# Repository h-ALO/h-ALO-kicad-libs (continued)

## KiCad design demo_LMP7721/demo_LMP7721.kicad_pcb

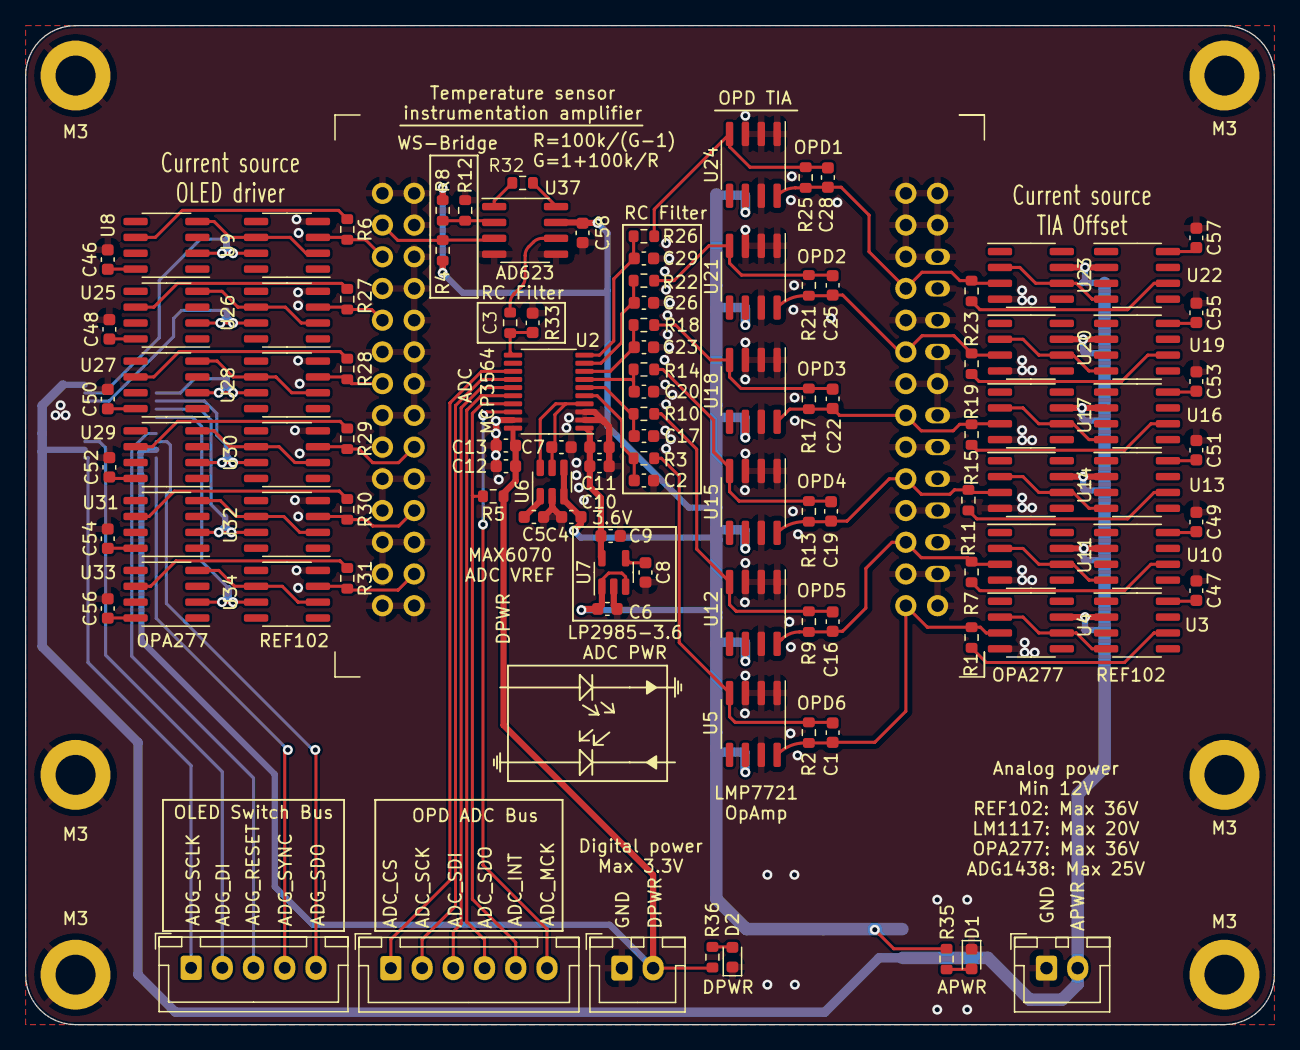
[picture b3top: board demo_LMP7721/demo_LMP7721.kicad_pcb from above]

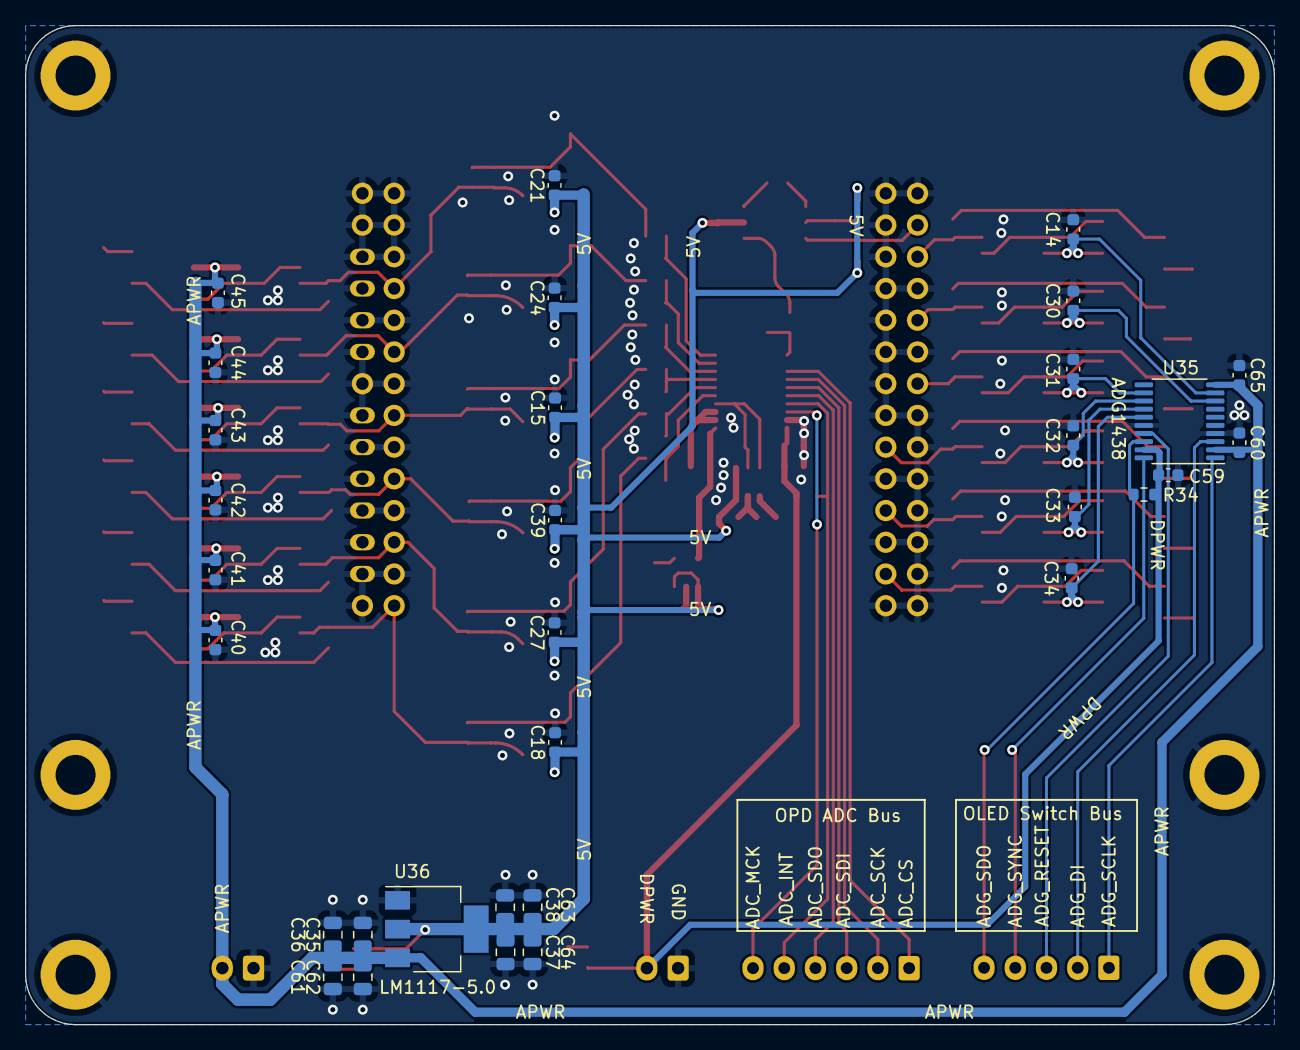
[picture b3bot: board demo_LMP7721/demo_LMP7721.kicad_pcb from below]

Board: 2 copper layers, 100.0 x 80.0 mm, 147 parts (32 on the bottom side), 93 nets.

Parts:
C1, C2, C3, C14, C15, C16, C17, C18, C19, C20, C21, C22, C23, C24, C25, C26, C27, C28, C29, C30, C31, C32, C33, C34, C39, C40, C41, C42, C43, C44, C45, C46, C47, C48, C49, C50, C51, C52, C53, C54, C55, C56, C57, C58: C; C_0603_1608Metric
C4, C5, C7, C10, C11, C12, C13, C59, C60, C65: 0.1µF; C_0603_1608Metric
C6: 1uF; C_0603_1608Metric
C8: 10nF; C_0603_1608Metric
C9: 2.2uF; C_0603_1608Metric
C35, C36, C37, C38, C61, C62, C63, C64: 1uF; C_0805_2012Metric
D1, D2: LED; LED_0603_1608Metric
H1, H2, H3, H4, H5, H6: MountingHole_Pad; MountingHole_3.2mm_M3_DIN965_Pad
J1, J3: Conn_01x02_Male; JST_XH_B2B-XH-A_1x02_P2.50mm_Vertical
J2: Conn_01x06_Male; JST_XH_B6B-XH-A_1x06_P2.50mm_Vertical
J4: Conn_01x05_Male; JST_XH_B5B-XH-A_1x05_P2.50mm_Vertical
R1, R2, R3, R4, R6, R7, R8, R9, R10, R11, R12, R13, R14, R15, R17, R18, R19, R21, R22, R23, R25, R26, R27, R28, R29, R30, R31, R32, R33, R34, R35, R36: R; R_0603_1608Metric
R5: 10k; R_0603_1608Metric
U1: h-ALO-sensor
U2: MCP3564-E/ST; TSSOP-20_4.4x6.5mm_P0.65mm
U3, U10, U13, U16, U19, U22: REF102CU; SOIC-8_3.9x4.9mm_P1.27mm
U4, U9, U11, U14, U17, U20, U23, U26, U28, U30, U32, U34: OPA277UA; SOIC-8_3.9x4.9mm_P1.27mm
U5, U12, U15, U18, U21, U24: LMP7721MA; SOIC-8_3.9x4.9mm_P1.27mm
U6: MAX6070AAUT12+T; SOT-23-6
U7: LP2985-3.3; SOT-23-5
U8, U25, U27, U29, U31, U33: REF102BU; SOIC-8_3.9x4.9mm_P1.27mm
U35: ADG1438BRUZ; TSSOP-20_4.4x6.5mm_P0.65mm
U36: LM1117-5.0; SOT-223-3_TabPin2
U37: AD623ARZ; SOIC-8_3.9x4.9mm_P1.27mm

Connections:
+5V: C4.1, C6.1, C15.2, C18.2, C21.2, C24.2, C27.2, C37.1, C38.1, C39.2, C58.1, C63.1, C64.1, R4.1, R8.1, R35.1, U5.6 (V+), U6.3 (EN), U6.4 (IN), U7.1 (VIN), U7.3 (ON/~OFF), U12.6 (V+), U15.6 (V+), U18.6 (V+), U21.6 (V+), U24.6 (V+), U36.2 (VO), U37.7 (Vs+)
/ADC_REFIN+: C7.1, U2.4 (REFIN+), U6.5 (OUTS), U6.6 (OUTF)
/OLED1+: R6.2, U1.5 (OLED1+), U9.3 (+IN)
/OLED2+: R27.2, U1.9 (OLED2+), U26.3 (+IN)
/OLED3+: R28.2, U1.13 (OLED3+), U28.3 (+IN)
/OLED4+: R29.2, U1.18 (OLED4+), U30.3 (+IN)
/OLED5+: R30.2, U1.22 (OLED5+), U32.3 (+IN)
/OLED6+: R31.2, U1.26 (OLED6+), U34.3 (+IN)
/OLED_driver0/V12: C14.1, U8.2 (Vin), U9.7 (V+), U35.9 (S4)
/OLED_driver1/V12: C30.1, U25.2 (Vin), U26.7 (V+), U35.8 (S3)
/OLED_driver2/V12: C31.1, U27.2 (Vin), U28.7 (V+), U35.12 (S8)
/OLED_driver3/V12: C32.1, U29.2 (Vin), U30.7 (V+), U35.13 (S7)
/OLED_driver4/V12: C33.1, U31.2 (Vin), U32.7 (V+), U35.14 (S6)
/OLED_driver5/V12: C34.1, U33.2 (Vin), U34.7 (V+), U35.15 (S5)
/OPD1-: C28.1, R23.1, R25.1, U1.36 (OPD1-), U23.3 (+IN), U24.8 (IN-)
/OPD2-: C25.1, R19.1, R21.1, U1.40 (OPD2-), U20.3 (+IN), U21.8 (IN-)
/OPD3-: C22.1, R15.1, R17.1, U1.44 (OPD3-), U17.3 (+IN), U18.8 (IN-)
/OPD4-: C19.1, R11.1, R13.1, U1.48 (OPD4-), U14.3 (+IN), U15.8 (IN-)
/OPD5-: C16.1, R7.1, R9.1, U1.52 (OPD5-), U11.3 (+IN), U12.8 (IN-)
/OPD6-: C1.1, R1.1, R2.1, U1.56 (OPD6-), U4.3 (+IN), U5.8 (IN-)
/Temp+: R4.2, U1.3 (Temp+), U37.3 (+)
/amp0/AMPO: C1.2, R2.2, R3.2, U5.4 (VO)
/amp1/AMPO: C16.2, R9.2, R10.2, U12.4 (VO)
/amp2/AMPO: C19.2, R13.2, R14.2, U15.4 (VO)
/amp3/AMPO: C22.2, R17.2, R18.2, U18.4 (VO)
/amp4/AMPO: C25.2, R21.2, R22.2, U21.4 (VO)
/amp5/AMPO: C28.2, R25.2, R26.2, U24.4 (VO)
ADC_AVDD: C9.1, C10.2, C11.2, U2.1 (AVDD), U7.5 (VOUT)
ADC_CH0: C2.2, R3.1, U2.5 (CH0)
ADC_CH1: C17.2, R10.1, U2.6 (CH1)
ADC_CH2: C20.2, R14.1, U2.7 (CH2)
ADC_CH3: C23.2, R18.1, U2.8 (CH3)
ADC_CH4: C26.2, R22.1, U2.9 (CH4)
ADC_CH5: C29.2, R26.1, U2.10 (CH5)
ADC_CH6: C3.1, R33.1, U2.11 (CH6)
ADC_CS: J2.1, U2.13 (*CS)
ADC_INT: J2.5, R5.2, U2.17 (*IRQ/MDAT)
ADC_MCK: J2.6, U2.18 (MCLKIN)
ADC_SCK: J2.2, U2.14 (SCK)
ADC_SDI: J2.3, U2.15 (SDI)
ADC_SDO: J2.4, U2.16 (SDO)
ADG_DI: J4.2, U35.3 (DIN)
ADG_RESET: J4.3, U35.17 (RESET)
ADG_SCLK: J4.1, U35.1 (SCLK)
ADG_SDO: J4.5, R34.2, U35.18 (SDO)
ADG_SYNC: J4.4, U35.20 (SYNC)
BATT_12V: C35.1, C36.1, C40.2, C41.2, C42.2, C43.2, C44.2, C45.2, C60.2, C61.1, C62.1, C65.2, J1.2, U3.2 (Vin), U4.7 (V+), U10.2 (Vin), U11.7 (V+), U13.2 (Vin), U14.7 (V+), U16.2 (Vin), U17.7 (V+), U19.2 (Vin), U20.7 (V+), U22.2 (Vin), U23.7 (V+), U35.2 (VDD), U35.10 (D), U36.3 (VI)
GND: C2.1, C3.2, C4.2, C5.2, C6.2, C7.2, C8.2, C9.2, C10.1, C11.1, C12.2, C13.2, C14.2, C15.1, C17.1, C18.1, C20.1, C21.1, C23.1, C24.1, C26.1, C27.1, C29.1, C30.2, C31.2, C32.2, C33.2, C34.2, C35.2, C36.2, C37.2, C38.2, C39.1, C40.1, C41.1, C42.1, C43.1, C44.1, C45.1, C46.2, C47.1, C48.2, C49.1, C50.2, C51.1, C52.2, C53.1, C54.2, C55.1, C56.2, C57.1, C58.2, C59.1, C60.1, C61.2, C62.2, C63.2, C64.2, C65.1, D1.1 (K), D2.1 (K), H1.1, H2.1, H3.1, H4.1, H5.1, H6.1, J1.1, J3.1, R12.2, U1.1 (NC), U1.2 (NC), U1.4 (NC), U1.6 (OPD1+), U1.7 (NC), U1.8 (NC), U1.10 (OPD2+), U1.11 (NC), U1.12 (NC), U1.14 (NC), U1.15 (OPD3+), U1.16 (NC), U1.17 (NC), U1.19 (OPD4+), U1.20 (NC), U1.21 (NC), U1.23 (OPD5+), U1.24 (NC), U1.25 (NC), U1.27 (OPD6+), U1.28 (NC), U1.29 (NC), U1.30 (NC), U1.31 (NC), U1.32 (Temp-), U1.33 (NC), U1.34 (NC), U1.35 (OLED1-), U1.37 (NC), U1.38 (NC), U1.39 (OLED2-), U1.41 (NC), U1.42 (NC), U1.43 (OLED3-), U1.45 (NC), U1.46 (NC), U1.47 (OLED4-), U1.49 (NC), U1.50 (NC), U1.51 (OLED5-), U1.53 (NC), U1.54 (NC), U1.55 (OLED6-), U2.2 (AGND), U2.3 (REFIN-), U2.19 (DGND), U4.4 (V-), U5.1 (IN+), U5.2 (NC), U5.3 (V-), U5.7 (NC), U6.2 (GND), U7.2 (GND), U9.4 (V-), U11.4 (V-), U12.1 (IN+), U12.2 (NC), U12.3 (V-), U12.7 (NC), U14.4 (V-), U15.1 (IN+), U15.2 (NC), U15.3 (V-), U15.7 (NC), U17.4 (V-), U18.1 (IN+), U18.2 (NC), U18.3 (V-), U18.7 (NC), U20.4 (V-), U21.1 (IN+), U21.2 (NC), U21.3 (V-), U21.7 (NC), U23.4 (V-), U24.1 (IN+), U24.2 (NC), U24.3 (V-), U24.7 (NC), U26.4 (V-), U28.4 (V-), U30.4 (V-), U32.4 (V-), U34.4 (V-), U35.4 (GND), U35.16 (VSS), U36.1 (GND), U37.4 (Vs-), U37.5 (Ref)
unnamed: C5.1, U6.1 (FILTER)
unnamed: C8.1, U7.4 (BP)
unnamed: C46.1, U8.8 (NR)
unnamed: C47.2, U3.8 (NR)
unnamed: C48.1, U25.8 (NR)
unnamed: C49.2, U10.8 (NR)
unnamed: C50.1, U27.8 (NR)
unnamed: C51.2, U13.8 (NR)
unnamed: C52.1, U29.8 (NR)
unnamed: C53.2, U16.8 (NR)
unnamed: C54.1, U31.8 (NR)
unnamed: C55.2, U19.8 (NR)
unnamed: C56.1, U33.8 (NR)
unnamed: C57.2, U22.8 (NR)
unnamed: D1.2 (A), R35.2
unnamed: D2.2 (A), R36.2
unnamed: R1.2, U3.6 (Vout)
unnamed: R6.1, U8.6 (Vout)
unnamed: R7.2, U10.6 (Vout)
unnamed: R11.2, U13.6 (Vout)
unnamed: R8.2, R12.1, U37.2 (-)
unnamed: R15.2, U16.6 (Vout)
unnamed: R19.2, U19.6 (Vout)
unnamed: R23.2, U22.6 (Vout)
unnamed: R27.1, U25.6 (Vout)
unnamed: R28.1, U27.6 (Vout)
unnamed: R29.1, U29.6 (Vout)
unnamed: R30.1, U31.6 (Vout)
unnamed: R31.1, U33.6 (Vout)
unnamed: R32.1, U37.8 (Rg)
unnamed: R32.2, U37.1 (Rg)
unnamed: R33.2, U37.6
unnamed: U3.4 (GND), U4.2 (-IN), U4.6 (OUTPUT)
unnamed: U8.4 (GND), U9.2 (-IN), U9.6 (OUTPUT)
unnamed: U10.4 (GND), U11.2 (-IN), U11.6 (OUTPUT)
unnamed: U13.4 (GND), U14.2 (-IN), U14.6 (OUTPUT)
unnamed: U16.4 (GND), U17.2 (-IN), U17.6 (OUTPUT)
unnamed: U19.4 (GND), U20.2 (-IN), U20.6 (OUTPUT)
unnamed: U22.4 (GND), U23.2 (-IN), U23.6 (OUTPUT)
unnamed: U25.4 (GND), U26.2 (-IN), U26.6 (OUTPUT)
unnamed: U27.4 (GND), U28.2 (-IN), U28.6 (OUTPUT)
unnamed: U29.4 (GND), U30.2 (-IN), U30.6 (OUTPUT)
unnamed: U31.4 (GND), U32.2 (-IN), U32.6 (OUTPUT)
unnamed: U33.4 (GND), U34.2 (-IN), U34.6 (OUTPUT)
VL: C12.1, C13.1, C59.2, J3.2, R5.1, R34.1, R36.1, U2.20 (DVDD), U35.19 (VL)

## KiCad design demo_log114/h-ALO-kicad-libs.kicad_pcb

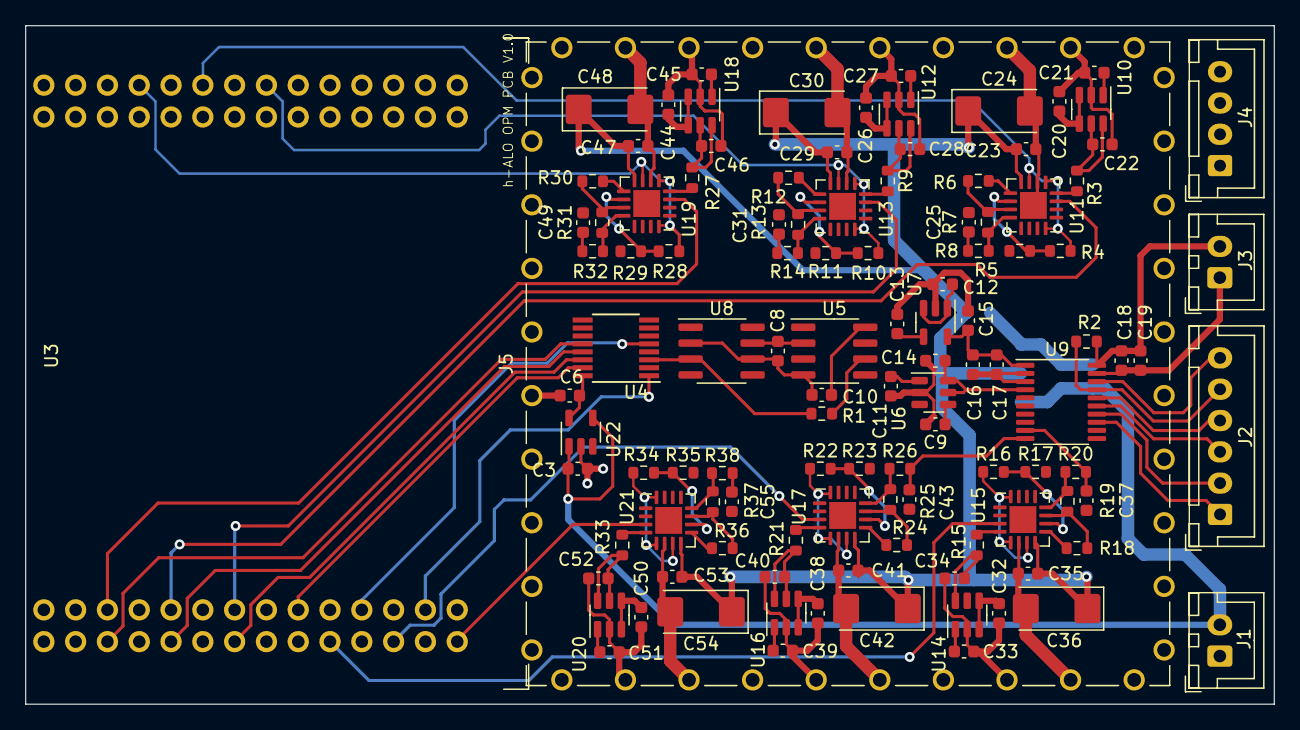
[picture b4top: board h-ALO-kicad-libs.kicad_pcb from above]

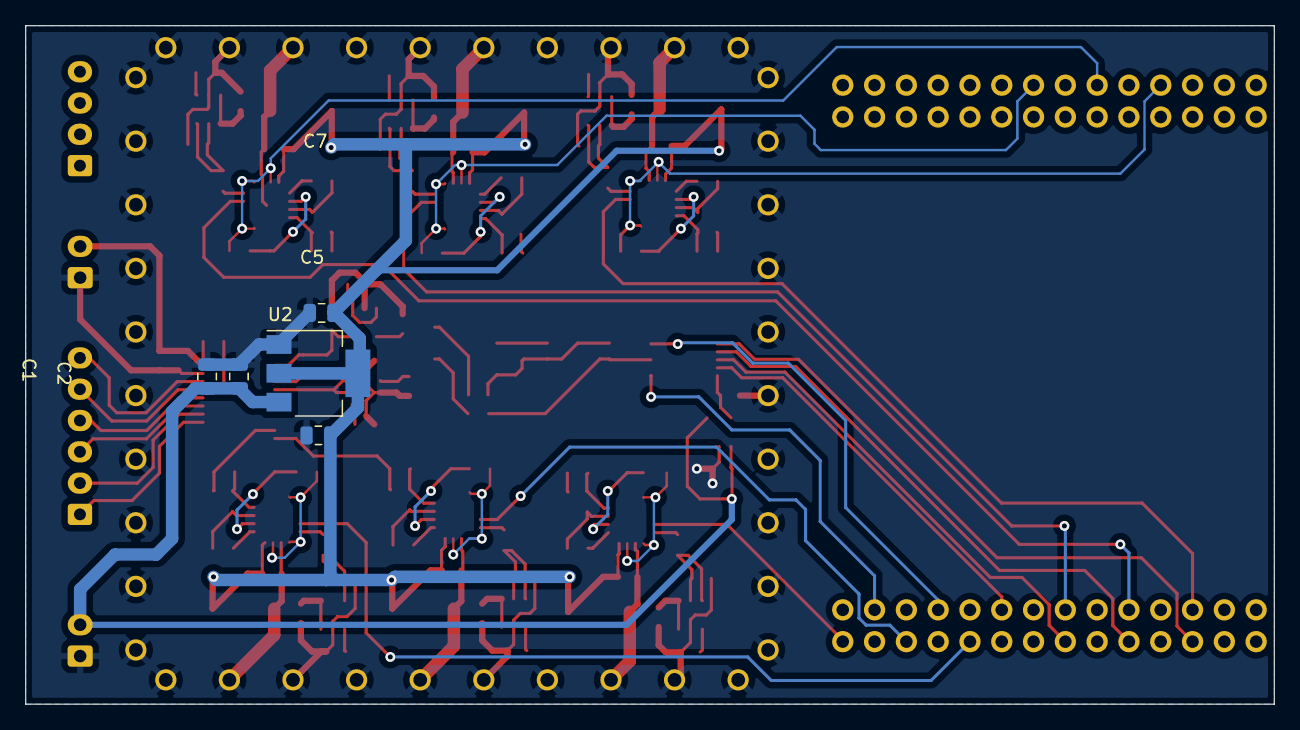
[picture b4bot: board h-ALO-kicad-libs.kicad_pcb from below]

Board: 2 copper layers, 99.7 x 54.2 mm, 118 parts (5 on the bottom side), 89 nets.

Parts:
C1, C2, C5, C7: 1uF; C_0805_2012Metric
C3, C12: 1uF; C_0603_1608Metric
C6, C8, C10, C25, C31, C37, C43, C49, C55: 1µF; C_0603_1608Metric
C9, C11, C14, C16, C17, C19, C20, C21, C22, C26, C27, C28, C32, C33, C34, C38, C39, C40, C44, C45, C46, C50, C51, C52: 0.1µF; C_0603_1608Metric
C13: 10nF; C_0603_1608Metric
C15: 2.2uF; C_0603_1608Metric
C18: 0.1uF; C_0603_1608Metric
C23, C29, C35, C41, C47, C53: 1000pF; C_0603_1608Metric
C24, C30, C36, C42, C48, C54: 10µF; CP_EIA-6032-15_Kemet-U
J1, J3: Conn_01x02_Male; JST_XH_B2B-XH-A_1x02_P2.50mm_Vertical
J2: Conn_01x06_Male; JST_XH_B6B-XH-A_1x06_P2.50mm_Vertical
J4: Conn_01x04_Male; JST_XH_B4B-XH-A_1x04_P2.50mm_Vertical
J5: RFShield_OnePiece; Wuerth_36503505_50x50mm
R1, R4, R5, R6, R7, R10, R11, R12, R13, R16, R17, R18, R19, R22, R23, R24, R25, R28, R29, R30, R31, R34, R35, R36, R37: R; R_0603_1608Metric
R2: 10k; R_0603_1608Metric
R3, R9, R15, R21, R27, R33: 1.62M; R_0603_1608Metric
R8, R14, R20, R26, R32, R38: 3k; R_0603_1608Metric
U2: LM1117-5.0; SOT-223-3_TabPin2
U3: h-ALO-sensor
U4: ADG658YRQZ-REEL7; QSOP-16_3.9x4.9mm_P0.635mm
U5: REF102BU; SOIC-8_3.9x4.9mm_P1.27mm
U6: MAX6070AAUT12+T; SOT-23-6
U7: LP2985-3.6; SOT-23-5
U8: OPA277UA; SOIC-8_3.9x4.9mm_P1.27mm
U9: MCP3564-E/ST; TSSOP-20_4.4x6.5mm_P0.65mm
U10, U12, U14, U16, U18, U20: MAX6070AAUT41+T; SOT-23-6
U11, U13, U15, U17, U19, U21: LOG114AIRGVR; QFN-16-1EP_4x4mm_P0.65mm_EP2.15x2.15mm
U22: MCP1804x-A002xOT; SOT-23-5

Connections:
+5V: C5.1, C7.1, C9.1, C12.1, C20.1, C23.1, C24.1, C26.1, C29.1, C30.1, C32.1, C35.1, C36.1, C38.1, C41.1, C42.1, C44.1, C47.1, C48.1, C50.1, C53.1, C54.1, U2.2 (VO), U6.3 (EN), U6.4 (IN), U7.1 (VIN), U7.3 (ON/~OFF), U10.3 (EN), U10.4 (IN), U11.8 (V+), U12.3 (EN), U12.4 (IN), U13.8 (V+), U14.3 (EN), U14.4 (IN), U15.8 (V+), U16.3 (EN), U16.4 (IN), U17.8 (V+), U18.3 (EN), U18.4 (IN), U19.8 (V+), U20.3 (EN), U20.4 (IN), U21.8 (V+)
/amp1/4.096V: C46.1, R27.1, U18.5 (OUTS), U18.6 (OUTF)
/amp1/+IN4: R28.2, R29.1, U19.10 (+IN4)
/amp1/-IN4: R30.2, R31.1, U19.11 (-IN4)
/amp1/I1: R27.2, U19.4 (I1)
/amp1/VLOGOUT: R30.1, U19.9 (VLOGOUT)
/amp1/VO4: R31.2, R32.1, U19.12 (VO4)
/amp2/4.096V: C22.1, R3.1, U10.5 (OUTS), U10.6 (OUTF)
/amp2/+IN4: R4.2, R5.1, U11.10 (+IN4)
/amp2/-IN4: R6.2, R7.1, U11.11 (-IN4)
/amp2/I1: R3.2, U11.4 (I1)
/amp2/VLOGOUT: R6.1, U11.9 (VLOGOUT)
/amp2/VO4: R7.2, R8.1, U11.12 (VO4)
/amp3/4.096V: C28.1, R9.1, U12.5 (OUTS), U12.6 (OUTF)
/amp3/+IN4: R10.2, R11.1, U13.10 (+IN4)
/amp3/-IN4: R12.2, R13.1, U13.11 (-IN4)
/amp3/I1: R9.2, U13.4 (I1)
/amp3/VLOGOUT: R12.1, U13.9 (VLOGOUT)
/amp3/VO4: R13.2, R14.1, U13.12 (VO4)
/amp4/4.096V: C34.1, R15.1, U14.5 (OUTS), U14.6 (OUTF)
/amp4/+IN4: R16.2, R17.1, U15.10 (+IN4)
/amp4/-IN4: R18.2, R19.1, U15.11 (-IN4)
/amp4/I1: R15.2, U15.4 (I1)
/amp4/VLOGOUT: R18.1, U15.9 (VLOGOUT)
/amp4/VO4: R19.2, R20.1, U15.12 (VO4)
/amp5/4.096V: C40.1, R21.1, U16.5 (OUTS), U16.6 (OUTF)
/amp5/+IN4: R22.2, R23.1, U17.10 (+IN4)
/amp5/-IN4: R24.2, R25.1, U17.11 (-IN4)
/amp5/I1: R21.2, U17.4 (I1)
/amp5/VLOGOUT: R24.1, U17.9 (VLOGOUT)
/amp5/VO4: R25.2, R26.1, U17.12 (VO4)
/amp6/4.096V: C52.1, R33.1, U20.5 (OUTS), U20.6 (OUTF)
/amp6/+IN4: R34.2, R35.1, U21.10 (+IN4)
/amp6/-IN4: R36.2, R37.1, U21.11 (-IN4)
/amp6/I1: R33.2, U21.4 (I1)
/amp6/VLOGOUT: R36.1, U21.9 (VLOGOUT)
/amp6/VO4: R37.2, R38.1, U21.12 (VO4)
ADC_AVDD: C15.1, C16.2, C17.2, U7.5 (VOUT), U9.1 (AVDD)
ADC_CH1: C49.1, R32.2, U9.6 (CH1)
ADC_CH2: C25.1, R8.2, U9.7 (CH2)
ADC_CH3: C31.1, R14.2, U9.8 (CH3)
ADC_CH4: C37.1, R20.2, U9.9 (CH4)
ADC_CH5: C43.1, R26.2, U9.10 (CH5)
ADC_CH6: C55.1, R38.2, U9.11 (CH6)
ADC_CS: J2.1, U9.13 (*CS)
ADC_DVDD: C18.1, C19.1, J3.2, R2.1, U9.20 (DVDD)
ADC_INT: J2.5, R2.2, U9.17 (*IRQ/MDAT)
ADC_MCK: J2.6, U9.18 (MCLKIN)
ADC_SCK: J2.2, U9.14 (SCK)
ADC_SDI: J2.3, U9.15 (SDI)
ADC_SDO: J2.4, U9.16 (SDO)
ADC_VREF+: C14.1, U6.5 (OUTS), U6.6 (OUTF), U9.4 (REFIN+)
BATT_+11V: C1.1, C2.1, C3.1, C8.1, J1.2, U2.3 (VI), U5.2 (Vin), U8.7 (V+), U22.1 (VIN), U22.4 (~SHDN)
GND: C1.2, C2.2, C3.2, C5.2, C6.2, C7.2, C9.2, C11.2, C12.2, C13.2, C14.2, C15.2, C16.1, C17.1, C18.2, C19.2, C20.2, C21.2, C22.2, C23.2, C24.2, C25.2, C26.2, C27.2, C28.2, C29.2, C30.2, C31.2, C32.2, C33.2, C34.2, C35.2, C36.2, C37.2, C38.2, C39.2, C40.2, C41.2, C42.2, C43.2, C44.2, C45.2, C46.2, C47.2, C48.2, C49.2, C50.2, C51.2, C52.2, C53.2, C54.2, C55.2, J1.1, J3.1, J5.1 (Shield), R5.2, R11.2, R17.2, R23.2, R29.2, R35.2, U2.1 (GND), U4.7 (VSS), U4.8 (GND), U6.2 (GND), U7.2 (GND), U8.4 (V-), U9.2 (AGND), U9.3 (REFIN-), U9.19 (DGND), U10.2 (GND), U11.6 (V-), U11.17 (V-), U12.2 (GND), U13.6 (V-), U13.17 (V-), U14.2 (GND), U15.6 (V-), U15.17 (V-), U16.2 (GND), U17.6 (V-), U17.17 (V-), U18.2 (GND), U19.6 (V-), U19.17 (V-), U20.2 (GND), U21.6 (V-), U21.17 (V-), U22.2 (GND)
MUX_VDD_+10V: C6.1, U4.16 (VDD), U22.5 (VOUT)
unnamed: C10.1, U5.8 (NR)
unnamed: C8.2, C10.2, U5.4 (GND), U8.2 (-IN), U8.6 (OUTPUT)
unnamed: C11.1, U6.1 (FILTER)
unnamed: C13.1, U7.4 (BP)
unnamed: C21.1, U10.1 (FILTER)
unnamed: C27.1, U12.1 (FILTER)
unnamed: C33.1, U14.1 (FILTER)
unnamed: C39.1, U16.1 (FILTER)
unnamed: C45.1, U18.1 (FILTER)
unnamed: C51.1, U20.1 (FILTER)
unnamed: R1.1, U5.6 (Vout)
OLED1+: U3.5 (OLED1+), U4.12 (S4)
OLED2+: U3.9 (OLED2+), U4.13 (S1)
OLED3+: U3.13 (OLED3+), U4.14 (S2)
OLED4+: U3.18 (OLED4+), U4.15 (S3)
OLED5+: U3.22 (OLED5+), U4.5 (S6)
OLED6+: U3.26 (OLED6+), U4.1 (S5)
OLED_A0: J4.4, U4.11 (A0)
OLED_A1: J4.3, U4.10 (A1)
OLED_A2: J4.2, U4.9 (A2)
OLED_CURRENT: R1.2, U4.3 (D), U8.3 (+IN)
OLED_EN: J4.1, U4.6 (EN)
OPD1+: U3.6 (OPD1+), U19.3 (I2)
OPD1-: R28.1, U3.36 (OPD1-), U19.5 (VCMIN), U19.7 (Com), U19.16 (VREF)
OPD2+: U3.10 (OPD2+), U11.3 (I2)
OPD2-: R4.1, U3.40 (OPD2-), U11.5 (VCMIN), U11.7 (Com), U11.16 (VREF)
OPD3+: U3.14 (OPD3+), U13.3 (I2)
OPD3-: R10.1, U3.44 (OPD3-), U13.5 (VCMIN), U13.7 (Com), U13.16 (VREF)
OPD4+: U3.19 (OPD4+), U15.3 (I2)
OPD4-: R16.1, U3.48 (OPD4-), U15.5 (VCMIN), U15.7 (Com), U15.16 (VREF)
OPD5+: U3.23 (OPD5+), U17.3 (I2)
OPD5-: R22.1, U3.52 (OPD5-), U17.5 (VCMIN), U17.7 (Com), U17.16 (VREF)
OPD6+: U3.27 (OPD6+), U21.3 (I2)
OPD6-: R34.1, U3.56 (OPD6-), U21.5 (VCMIN), U21.7 (Com), U21.16 (VREF)

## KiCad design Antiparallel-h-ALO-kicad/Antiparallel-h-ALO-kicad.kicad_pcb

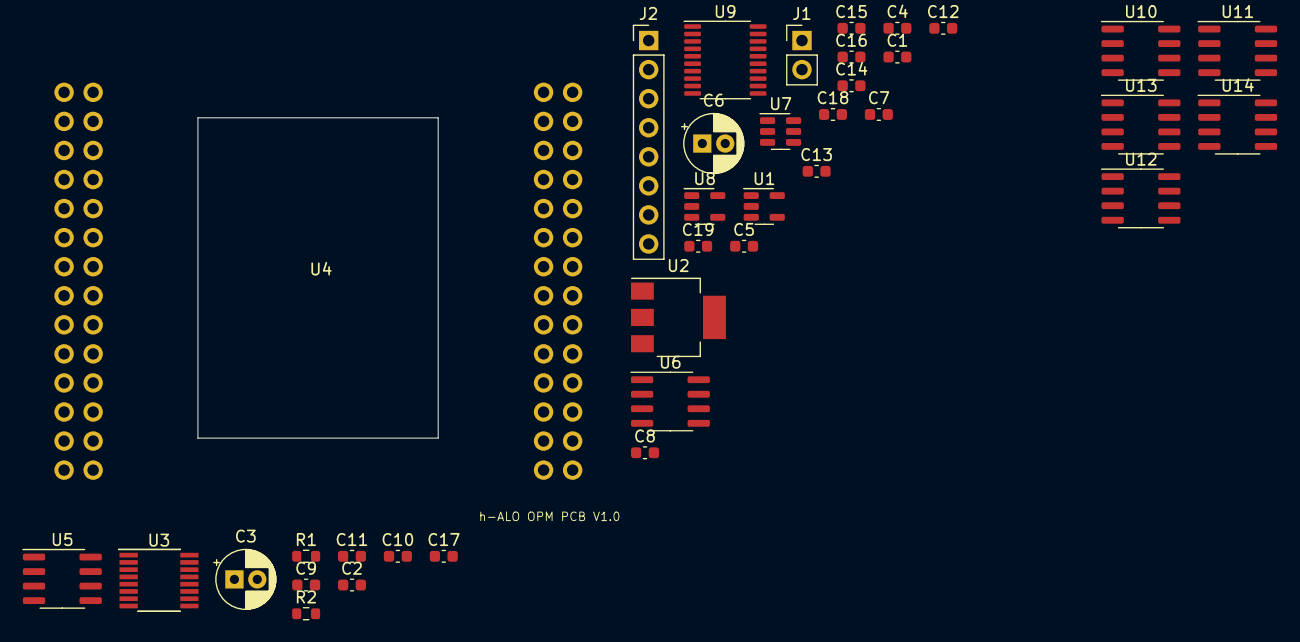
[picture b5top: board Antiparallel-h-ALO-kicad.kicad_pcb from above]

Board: 2 copper layers, 37 parts (0 on the bottom side), 27 nets, no tracks yet.

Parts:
C1, C2, C7, C12: 1uF; C_0603_1608Metric
C3, C6: C_Polarized; CP_Radial_D5.0mm_P2.00mm
C4, C13: 10nF; C_0603_1608Metric
C5, C15: 2.2uF; C_0603_1608Metric
C8, C9: 1µF; C_0603_1608Metric
C10, C11, C14, C16, C17, C19: 0.1µF; C_0603_1608Metric
C18: 0.1uF; C_0603_1608Metric
J1: Conn_01x02_Male; PinHeader_1x02_P2.54mm_Vertical
J2: Conn_01x08_Male; PinHeader_1x08_P2.54mm_Vertical
R1: R; R_0603_1608Metric
R2: 10k; R_0603_1608Metric
U1: LP2985-10.0; SOT-23-5
U2: LM1117-5.0; SOT-223-3_TabPin2
U3: ADG658YRQZ-REEL7; QSOP-16_3.9x4.9mm_P0.635mm
U4: h-ALO-sensor
U5: REF102BU; SOIC-8_3.9x4.9mm_P1.27mm
U6, U10, U11, U12, U13, U14: OPA277UA; SOIC-8_3.9x4.9mm_P1.27mm
U7: MAX6070AAUT12+T; SOT-23-6
U8: LP2985-3.6; SOT-23-5
U9: MCP3564-E/ST; TSSOP-20_4.4x6.5mm_P0.65mm

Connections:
+5V: C6.1, C7.1, C10.1, C12.1, U2.2 (VO), U7.3 (EN), U7.4 (IN), U8.1 (VIN), U8.3 (ON/~OFF)
ADC_AVDD: C15.1, C16.2, C17.2, U8.5 (VOUT), U9.1 (AVDD)
ADC_CS: J2.8, U9.13 (*CS)
ADC_DVDD: C18.1, C19.1, J2.2, R2.1, U9.20 (DVDD)
ADC_INT: J2.4, R2.2, U9.17 (*IRQ/MDAT)
ADC_MCK: J2.3, U9.18 (MCLKIN)
ADC_SCK: J2.7, U9.14 (SCK)
ADC_SDI: J2.6, U9.15 (SDI)
ADC_SDO: J2.5, U9.16 (SDO)
ADC_VREF+: C14.1, U7.5 (OUTS), U7.6 (OUTF), U9.4 (REFIN+)
BATT_+11V: C1.1, C2.1, C3.1, C8.1, J1.2, U1.1 (VIN), U1.3 (ON/~OFF), U2.3 (VI), U5.2 (Vin), U6.7 (V+)
MUX_VDD_+10V: C5.1, U1.5 (VOUT), U3.16 (VDD)
unnamed: C4.1, U1.4 (BP)
unnamed: C8.2, U5.4 (GND), U6.2 (-IN), U6.6 (OUTPUT)
unnamed: C9.1, U5.8 (NR)
unnamed: C11.1, U7.1 (FILTER)
unnamed: C13.1, U8.4 (BP)
unnamed: R1.1, U5.6 (Vout)
OLED1+: U3.13 (S1), U4.5 (OLED1+)
OLED2+: U3.14 (S2), U4.9 (OLED2+)
OLED3+: U3.15 (S3), U4.13 (OLED3+)
OLED4+: U3.12 (S4), U4.18 (OLED4+)
OLED5+: U3.1 (S5), U4.22 (OLED5+)
OLED6+: U3.5 (S6), U4.26 (OLED6+)
OLED_CURRENT: R1.2, U3.3 (D), U6.3 (+IN)
OPD1+: U4.6 (OPD1+), U4.10 (OPD2+), U4.14 (OPD3+), U4.19 (OPD4+), U4.23 (OPD5+), U4.56 (OPD6-), U10.3 (+IN), U11.3 (+IN), U12.3 (+IN), U13.3 (+IN), U14.3 (+IN)
OPD1-: C1.2, C2.2, C3.2, C4.2, C5.2, C6.2, C7.2, C9.2, C10.2, C11.2, C12.2, C13.2, C14.2, C15.2, C16.1, C17.1, C18.2, C19.2, J1.1, J2.1, U1.2 (GND), U2.1 (GND), U3.7 (VSS), U3.8 (GND), U4.27 (OPD6+), U4.36 (OPD1-), U4.40 (OPD2-), U4.44 (OPD3-), U4.48 (OPD4-), U4.52 (OPD5-), U6.4 (V-), U7.2 (GND), U8.2 (GND), U9.2 (AGND), U9.3 (REFIN-), U9.19 (DGND)

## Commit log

2022-10-14 init
2022-10-19 Updated h-ALO footprint
2022-10-24 Added ADG658
2022-10-24 Update ADG658
2022-11-01 update antiparallel_circuit
2022-11-04 added offset schematics
2022-12-07 updates values
2022-12-22 refactor and set bycap values
2023-02-14 update to 7
